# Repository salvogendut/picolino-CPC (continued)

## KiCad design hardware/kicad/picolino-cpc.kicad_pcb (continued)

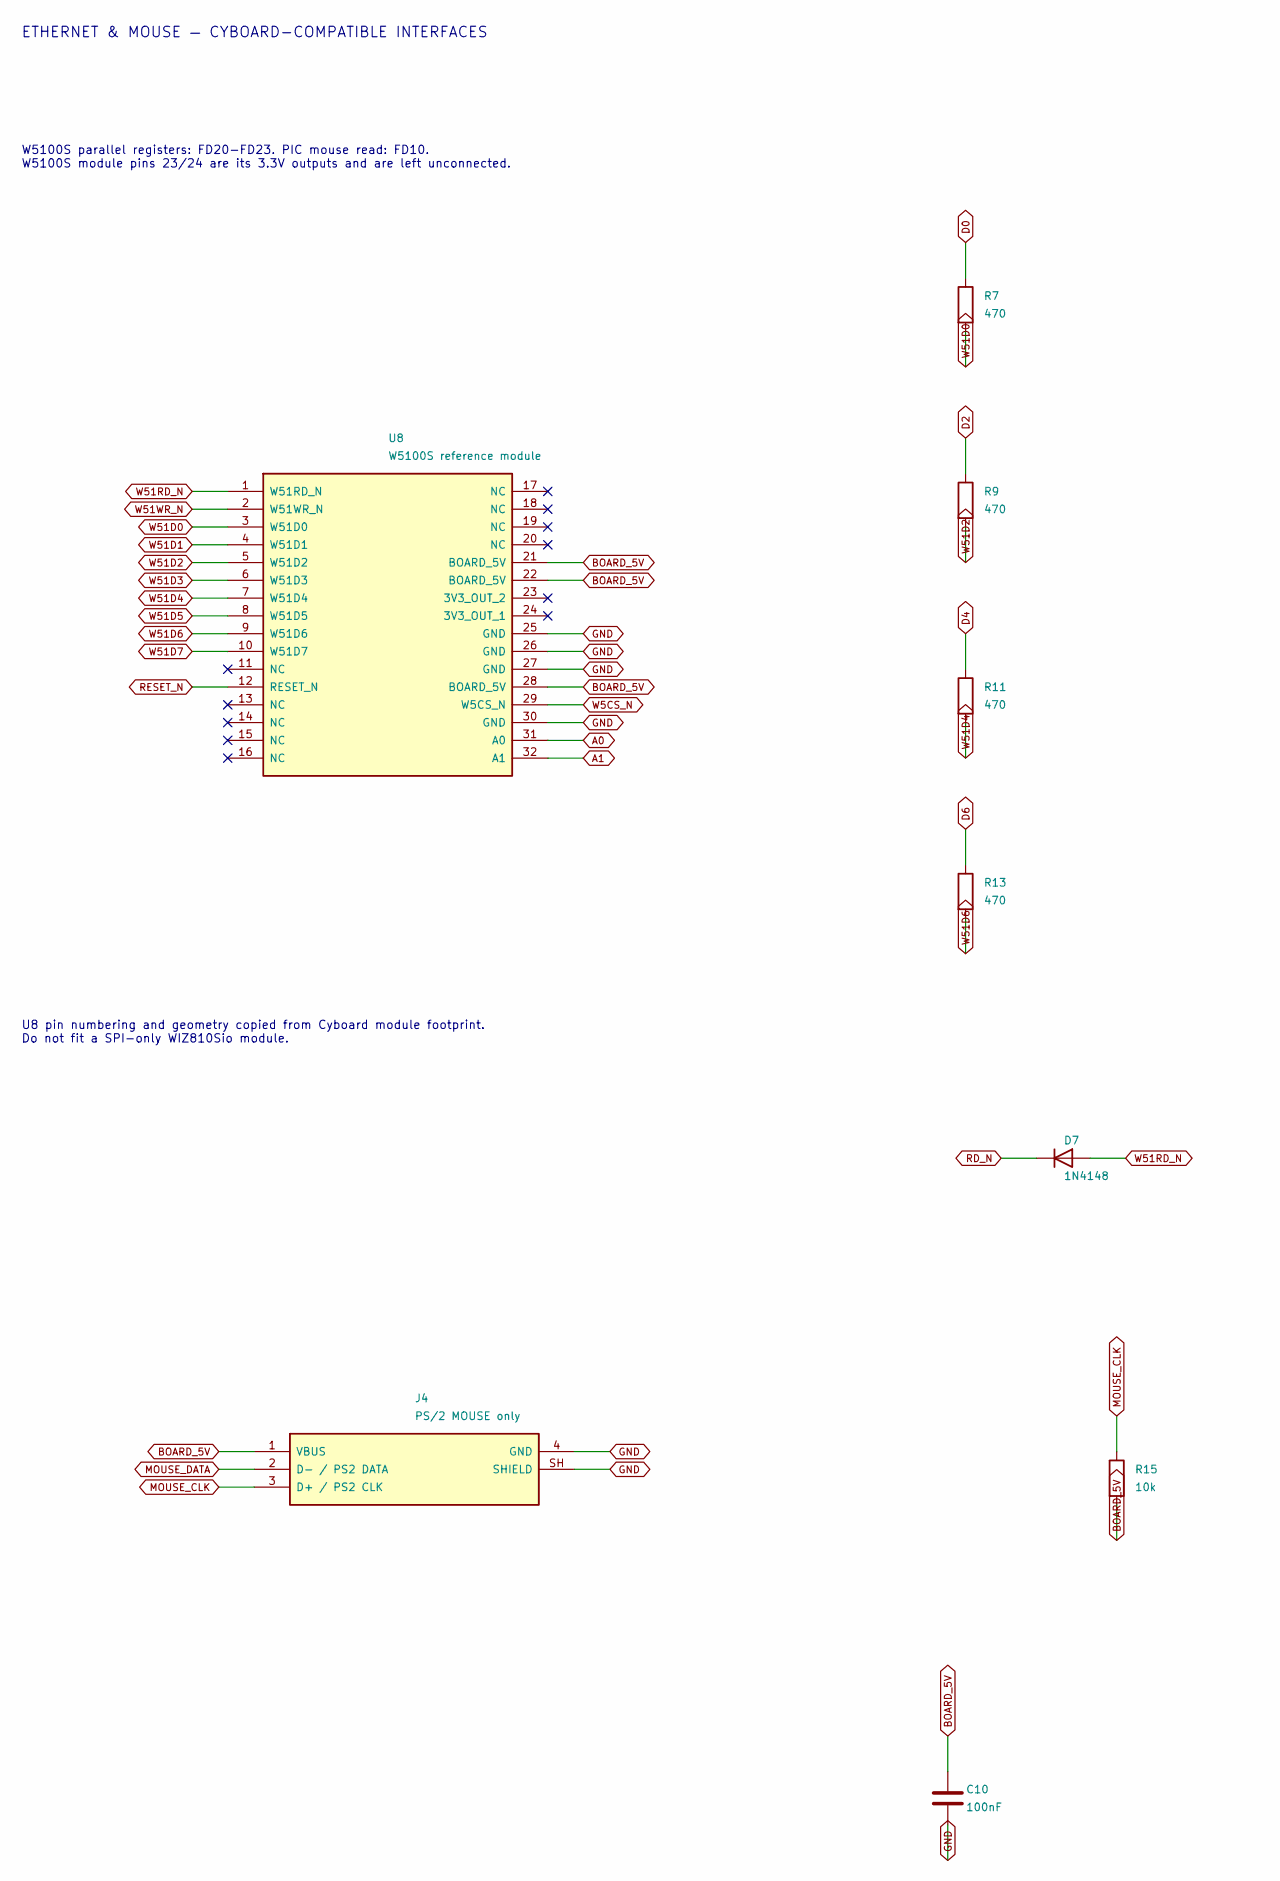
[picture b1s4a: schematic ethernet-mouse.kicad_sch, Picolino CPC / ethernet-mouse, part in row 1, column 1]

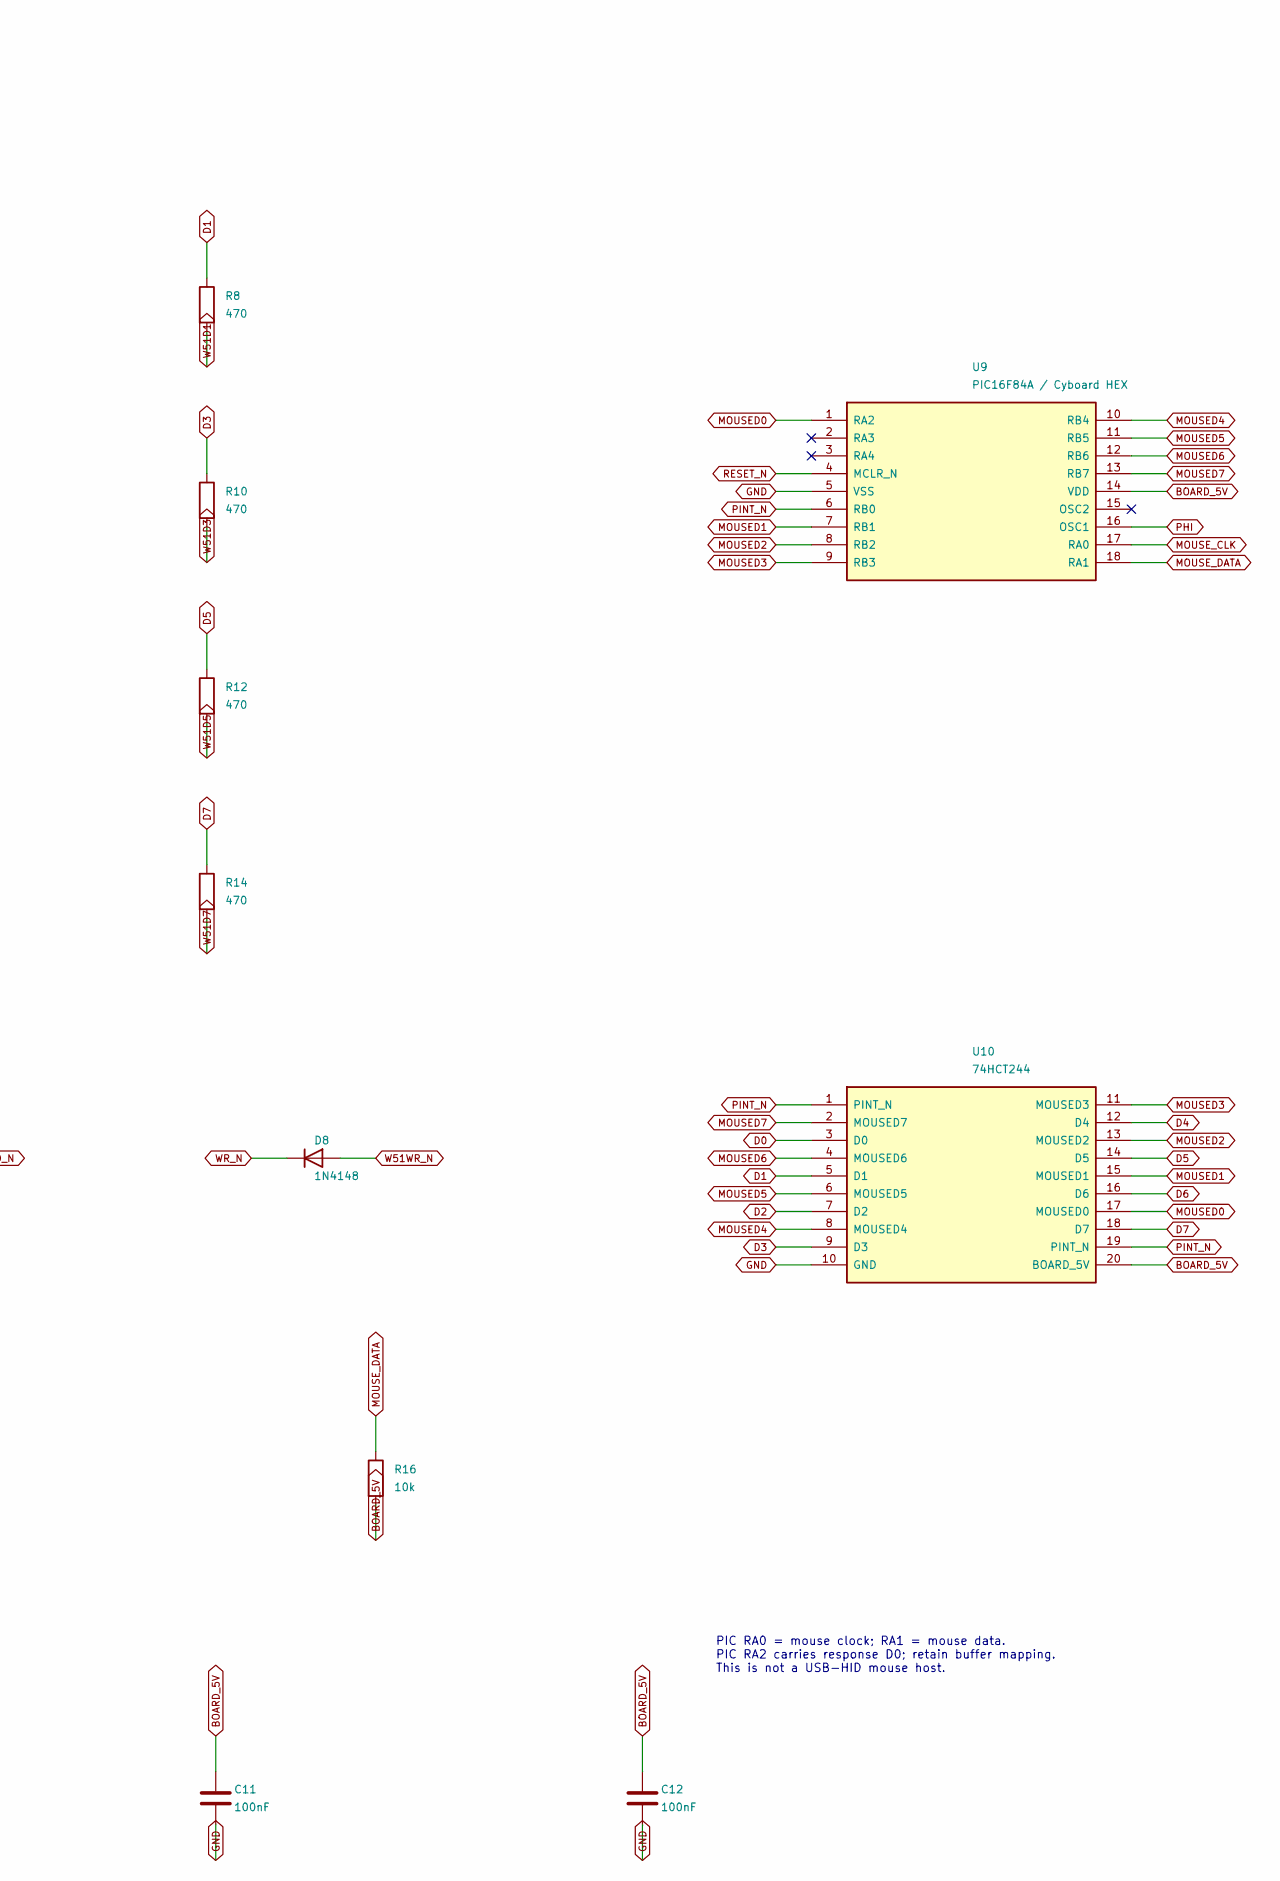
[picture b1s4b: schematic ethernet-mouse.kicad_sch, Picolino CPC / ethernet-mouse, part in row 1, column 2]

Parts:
C10, C11, C12: 100nF; C_0805_2012Metric
D7, D8: 1N4148; D_DO-35_SOD27_P7.62mm_Horizontal
J4: PS/2 MOUSE only; USB_A_TE_292303-7_Horizontal
R7, R8, R9, R10, R11, R12, R13, R14: 470; R_0805_2012Metric
R15, R16: 10k; R_0805_2012Metric
U8: W5100S reference module; W5100S_Cyboard
U9: PIC16F84A / Cyboard HEX; DIP-18_W7.62mm_Socket_LongPads
U10: 74HCT244; DIP-20_W7.62mm_Socket_LongPads

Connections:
A0: U8.31 (A0); also elsewhere on the board
A1: U8.32 (A1); also elsewhere on the board
BOARD_5V: C10.1, C11.1, C12.1, J4.1 (VBUS), R15.2, R16.2, U8.21 (BOARD_5V), U8.22 (BOARD_5V), U8.28 (BOARD_5V), U9.14 (VDD), U10.20 (BOARD_5V); also elsewhere on the board
D0: R7.1, U10.3 (D0); also elsewhere on the board
D1: R8.1, U10.5 (D1); also elsewhere on the board
D2: R9.1, U10.7 (D2); also elsewhere on the board
D3: R10.1, U10.9 (D3); also elsewhere on the board
D4: R11.1, U10.12 (D4); also elsewhere on the board
D5: R12.1, U10.14 (D5); also elsewhere on the board
D6: R13.1, U10.16 (D6); also elsewhere on the board
D7: R14.1, U10.18 (D7); also elsewhere on the board
GND: C10.2, C11.2, C12.2, J4.4 (GND), J4.SH (SHIELD), U8.25 (GND), U8.26 (GND), U8.27 (GND), U8.30 (GND), U9.5 (VSS), U10.10 (GND); also elsewhere on the board
MOUSED0: U9.1 (RA2), U10.17 (MOUSED0)
MOUSED1: U9.7 (RB1), U10.15 (MOUSED1)
MOUSED2: U9.8 (RB2), U10.13 (MOUSED2)
MOUSED3: U9.9 (RB3), U10.11 (MOUSED3)
MOUSED4: U9.10 (RB4), U10.8 (MOUSED4)
MOUSED5: U9.11 (RB5), U10.6 (MOUSED5)
MOUSED6: U9.12 (RB6), U10.4 (MOUSED6)
MOUSED7: U9.13 (RB7), U10.2 (MOUSED7)
MOUSE_CLK: J4.3 (D+ / PS2 CLK), R15.1, U9.17 (RA0)
MOUSE_DATA: J4.2 (D- / PS2 DATA), R16.1, U9.18 (RA1)
PHI: U9.16 (OSC1); also elsewhere on the board
PINT_N: U9.6 (RB0), U10.1 (PINT_N), U10.19 (PINT_N); also elsewhere on the board
RD_N: D7.1 (K); also elsewhere on the board
RESET_N: U8.12 (RESET_N), U9.4 (MCLR_N); also elsewhere on the board
W5CS_N: U8.29 (W5CS_N); also elsewhere on the board
W51D0: R7.2, U8.3 (W51D0)
W51D1: R8.2, U8.4 (W51D1)
W51D2: R9.2, U8.5 (W51D2)
W51D3: R10.2, U8.6 (W51D3)
W51D4: R11.2, U8.7 (W51D4)
W51D5: R12.2, U8.8 (W51D5)
W51D6: R13.2, U8.9 (W51D6)
W51D7: R14.2, U8.10 (W51D7)
W51RD_N: D7.2 (A), U8.1 (W51RD_N)
W51WR_N: D8.2 (A), U8.2 (W51WR_N)
WR_N: D8.1 (K); also elsewhere on the board

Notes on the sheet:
ETHERNET & MOUSE — CYBOARD-COMPATIBLE INTERFACES
W5100S parallel registers: FD20-FD23. PIC mouse read: FD10. W5100S module pins 23/24 are its 3.3V outputs and are left unconnected.
U8 pin numbering and geometry copied from Cyboard module footprint. Do not fit a SPI-only WIZ810Sio module.
PIC RA0 = mouse clock; RA1 = mouse data. PIC RA2 carries response D0; retain buffer mapping. This is not a USB-HID mouse host.

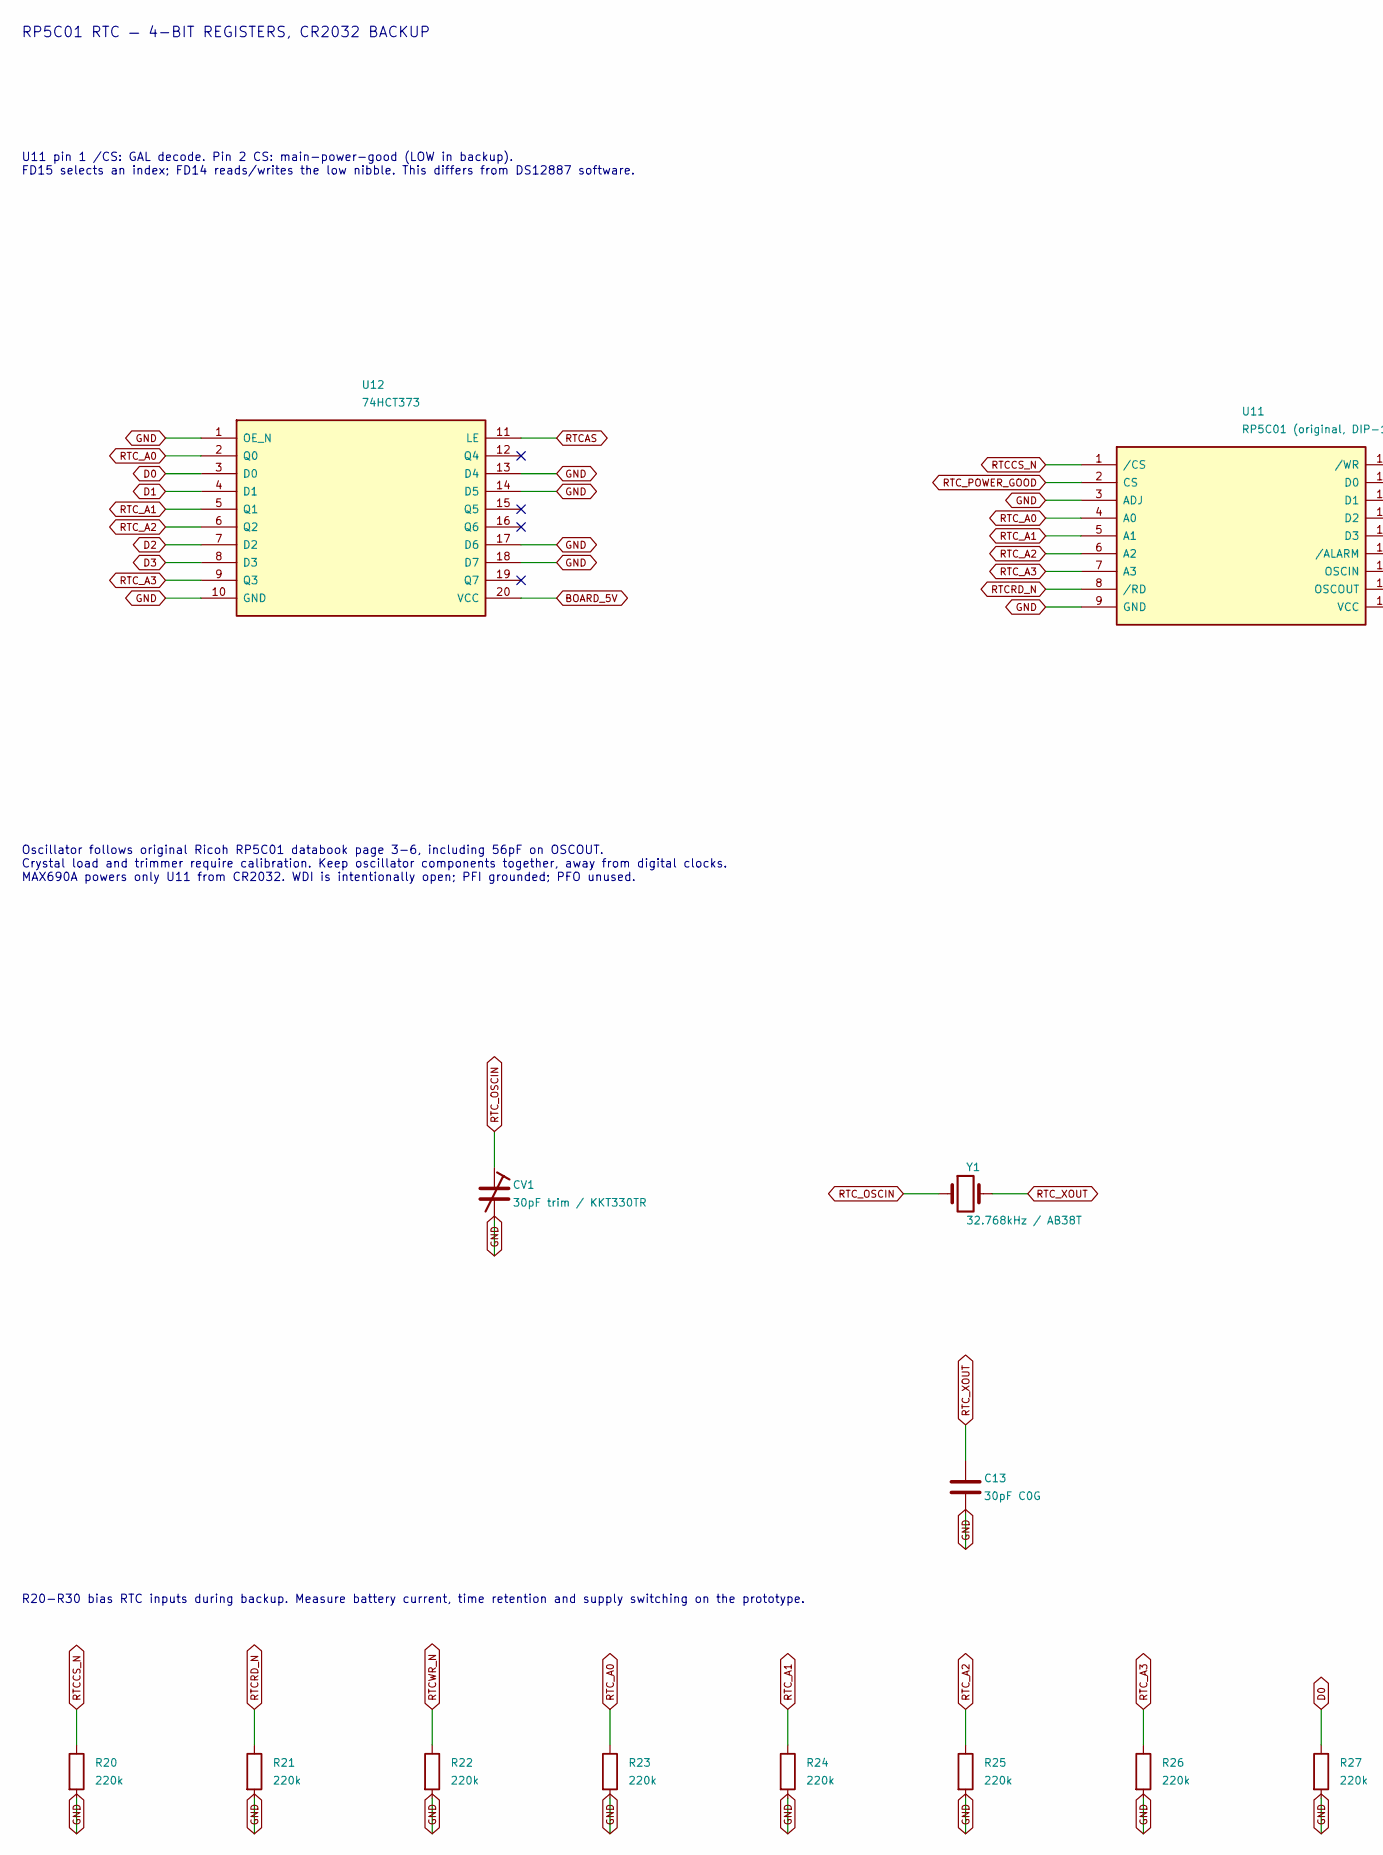
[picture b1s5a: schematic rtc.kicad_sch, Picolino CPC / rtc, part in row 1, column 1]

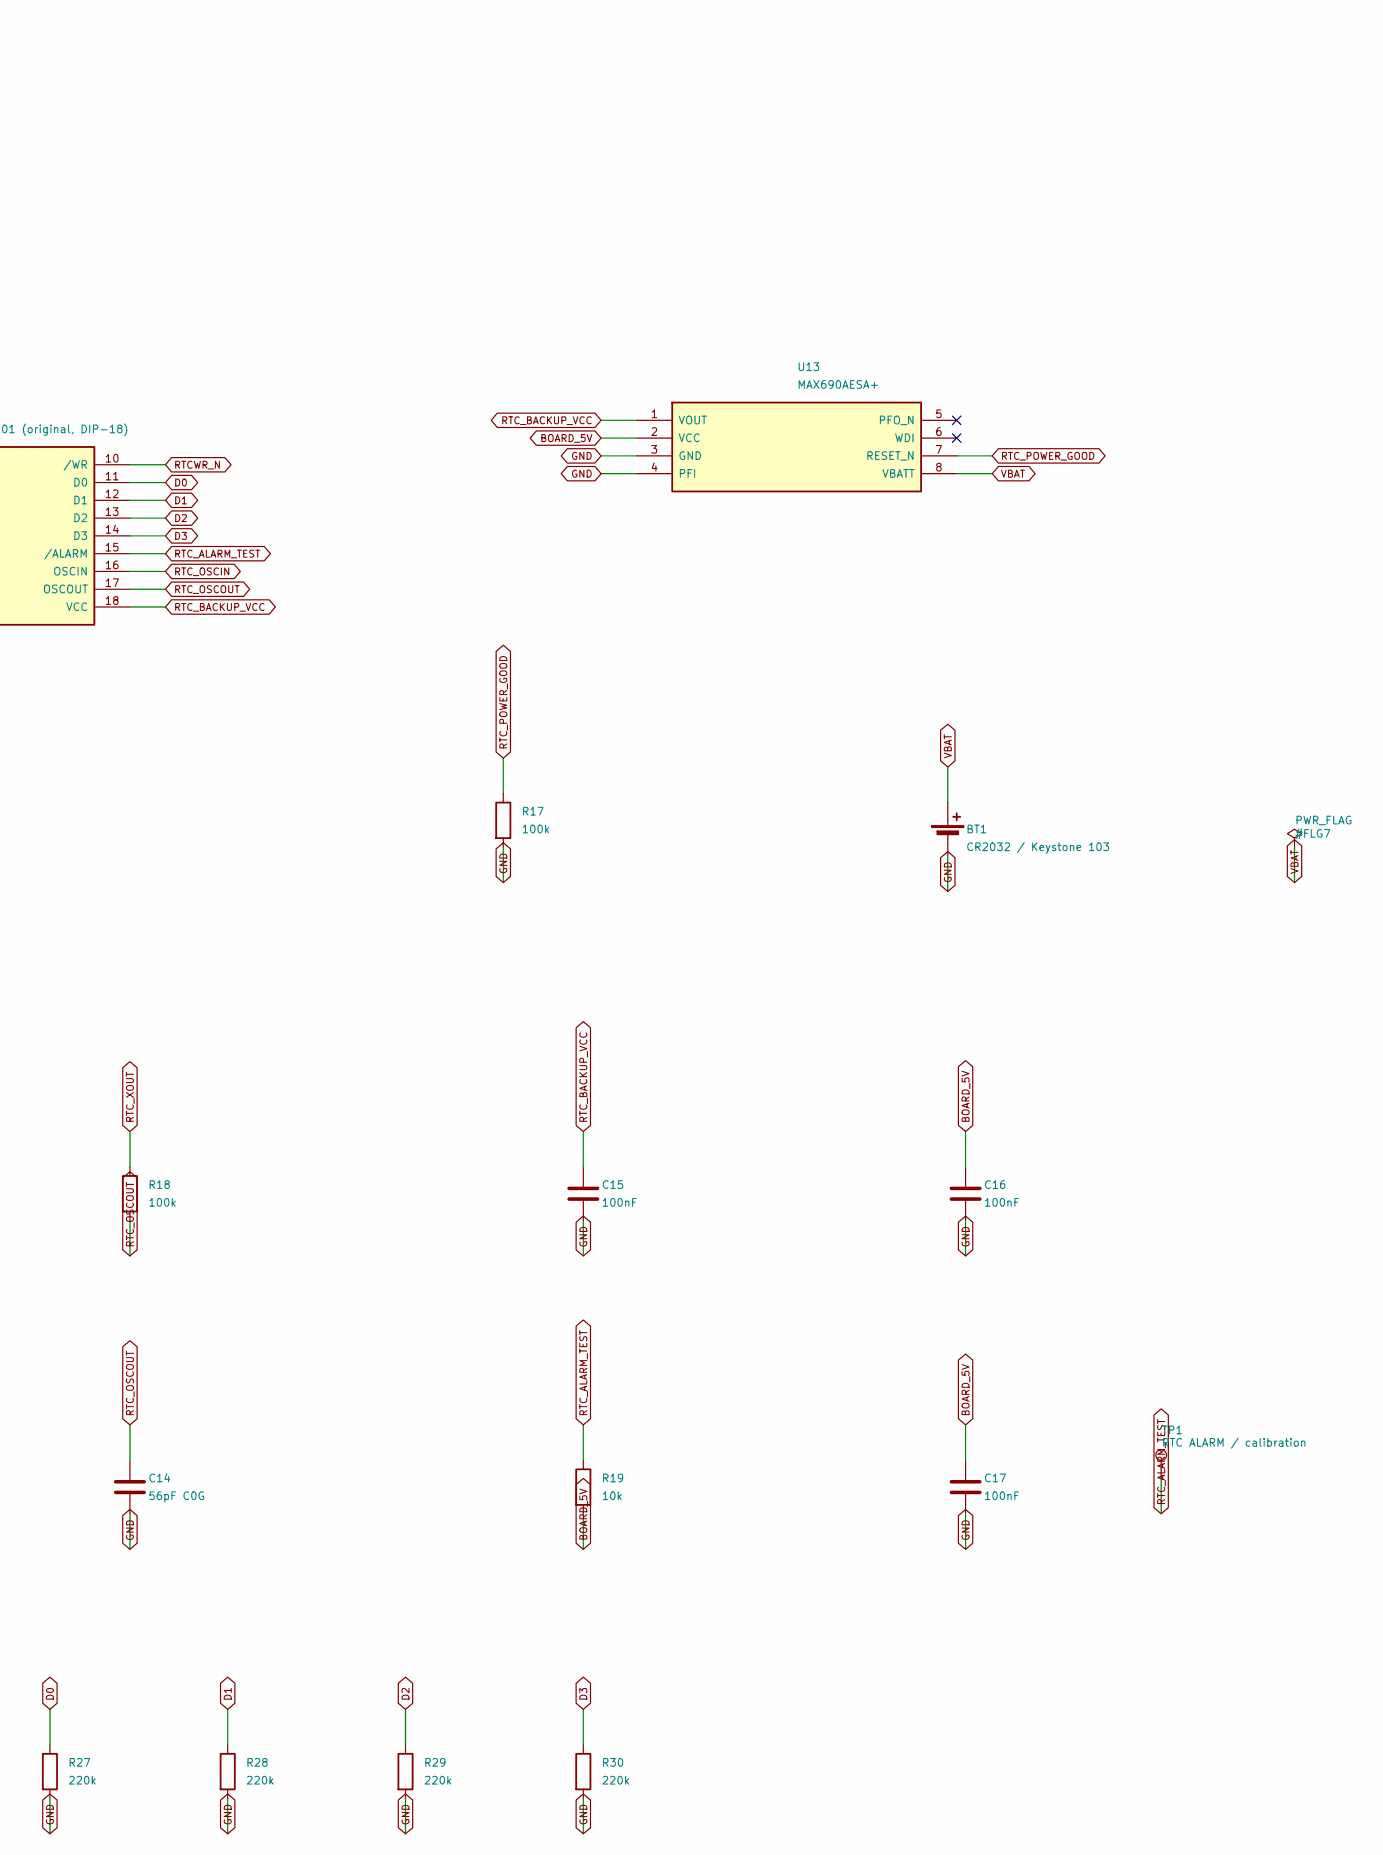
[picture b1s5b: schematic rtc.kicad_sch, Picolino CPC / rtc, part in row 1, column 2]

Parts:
BT1: CR2032 / Keystone 103; BatteryHolder_Keystone_103_1x20mm
C13: 30pF C0G; C_0805_2012Metric
C14: 56pF C0G; C_0805_2012Metric
C15, C16, C17: 100nF; C_0805_2012Metric
CV1: 30pF trim / KKT330TR; C_Trimmer_Murata_TZC3
R17, R18: 100k; R_0805_2012Metric
R19: 10k; R_0805_2012Metric
R20, R21, R22, R23, R24, R25, R26, R27, R28, R29, R30: 220k; R_0805_2012Metric
TP1: RTC ALARM / calibration; TestPoint_THTPad_D2.0mm_Drill1.0mm
U11: RP5C01 (original, DIP-18); DIP-18_W7.62mm_Socket_LongPads
U12: 74HCT373; DIP-20_W7.62mm_Socket_LongPads
U13: MAX690AESA+; SOIC-8_3.9x4.9mm_P1.27mm
Y1: 32.768kHz / AB38T; Crystal_C38-LF_D3.0mm_L8.0mm_Vertical

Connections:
BOARD_5V: C16.1, C17.1, R19.2, U12.20 (VCC), U13.2 (VCC); also elsewhere on the board
D0: R27.1, U11.11 (D0), U12.3 (D0); also elsewhere on the board
D1: R28.1, U11.12 (D1), U12.4 (D1); also elsewhere on the board
D2: R29.1, U11.13 (D2), U12.7 (D2); also elsewhere on the board
D3: R30.1, U11.14 (D3), U12.8 (D3); also elsewhere on the board
GND: BT1.2 (-), C13.2, C14.2, C15.2, C16.2, C17.2, CV1.2, R17.2, R20.2, R21.2, R22.2, R23.2, R24.2, R25.2, R26.2, R27.2, R28.2, R29.2, R30.2, U11.3 (ADJ), U11.9 (GND), U12.1 (OE_N), U12.10 (GND), U12.13 (D4), U12.14 (D5), U12.17 (D6), U12.18 (D7), U13.3 (GND), U13.4 (PFI); also elsewhere on the board
RTCAS: U12.11 (LE); also elsewhere on the board
RTCCS_N: R20.1, U11.1 (/CS); also elsewhere on the board
RTCRD_N: R21.1, U11.8 (/RD); also elsewhere on the board
RTCWR_N: R22.1, U11.10 (/WR); also elsewhere on the board
RTC_A0: R23.1, U11.4 (A0), U12.2 (Q0)
RTC_A1: R24.1, U11.5 (A1), U12.5 (Q1)
RTC_A2: R25.1, U11.6 (A2), U12.6 (Q2)
RTC_A3: R26.1, U11.7 (A3), U12.9 (Q3)
RTC_ALARM_TEST: R19.1, TP1.1, U11.15 (/ALARM)
RTC_BACKUP_VCC: C15.1, U11.18 (VCC), U13.1 (VOUT)
RTC_OSCIN: CV1.1, U11.16 (OSCIN), Y1.1
RTC_OSCOUT: C14.1, R18.2, U11.17 (OSCOUT)
RTC_POWER_GOOD: R17.1, U11.2 (CS), U13.7 (RESET_N)
RTC_XOUT: C13.1, R18.1, Y1.2
VBAT: BT1.1 (+), U13.8 (VBATT)

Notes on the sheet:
RP5C01 RTC — 4-BIT REGISTERS, CR2032 BACKUP
U11 pin 1 /CS: GAL decode. Pin 2 CS: main-power-good (LOW in backup). FD15 selects an index; FD14 reads/writes the low nibble. This differs from DS12887 software.
Oscillator follows original Ricoh RP5C01 databook page 3-6, including 56pF on OSCOUT. Crystal load and trimmer require calibration. Keep oscillator components together, away from digital clocks. MAX690A powers only U11 from CR2032. WDI is intentionally open; PFI grounded; PFO unused.
R20-R30 bias RTC inputs during backup. Measure battery current, time retention and supply switching on the prototype.

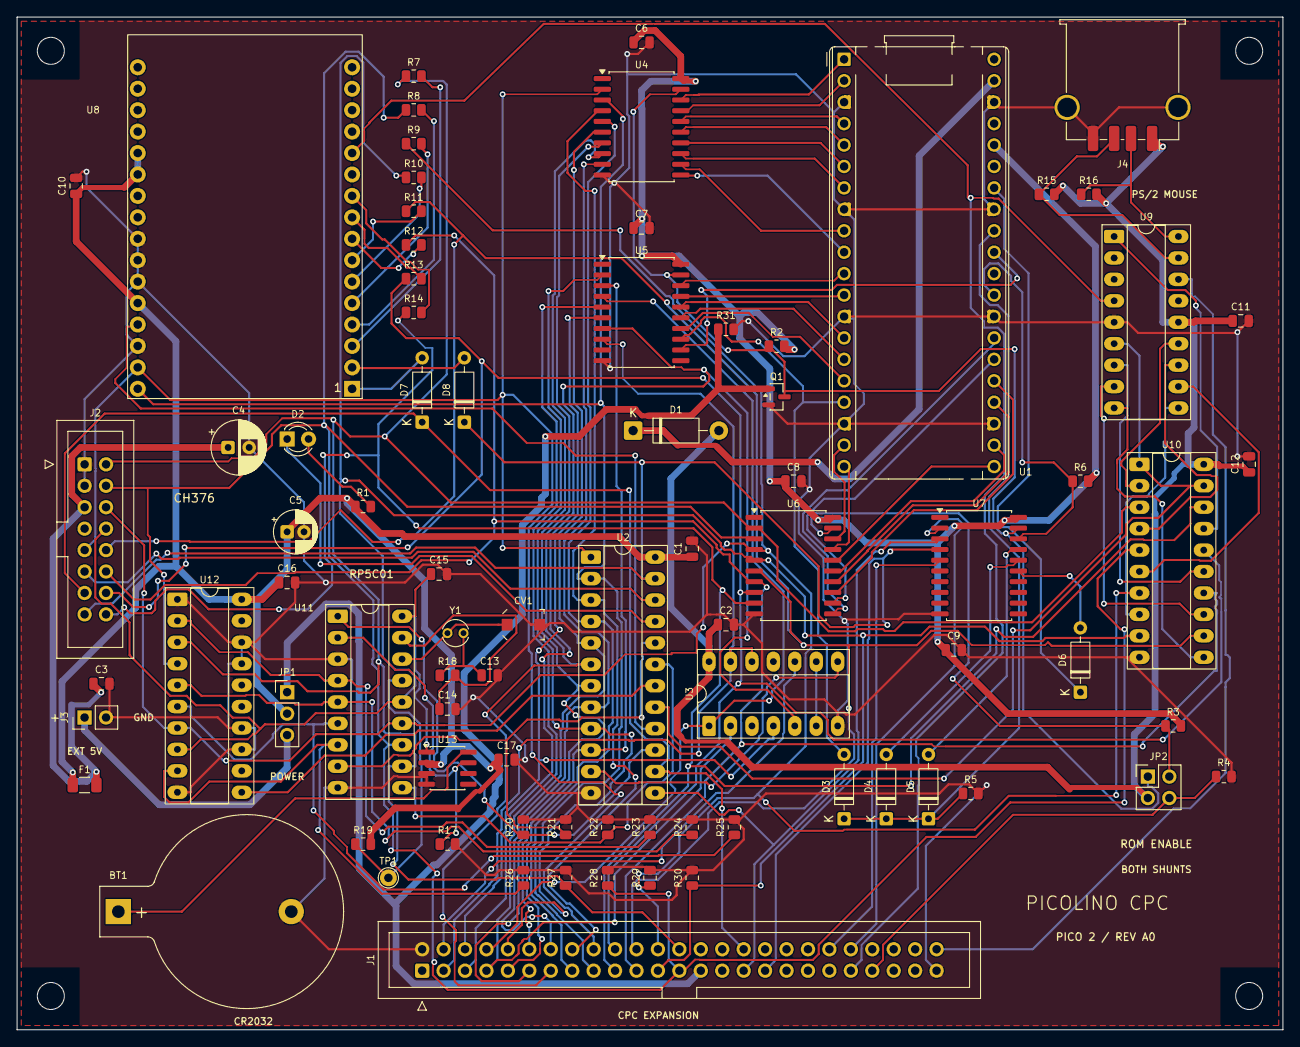
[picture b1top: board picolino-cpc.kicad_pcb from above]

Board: 2 copper layers, 150.0 x 120.0 mm, 85 parts (0 on the bottom side), 112 nets.

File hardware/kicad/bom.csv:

Reference,Value,Footprint,Assembly note
J1,CPC 50-pin expansion,Picolino:IDC-Header_2x25_P2.54mm_Vertical,CPC/Mother X4 contact numbers; short 50-way cable. Pin 1 marked on silk.
U2,GAL20V8B / picolino.jed,Picolino:DIP-24_W7.62mm_Socket_LongPads,Program firmware/gal/picolino.pld before fitting.
U3,74HCT21,Picolino:DIP-14_W7.62mm_Socket_LongPads,
J2,CH376 parallel / short ribbon,Picolino:IDC-Header_2x08_P2.54mm_Vertical,CPC_PICOROM J2 pinout. External reference CH376 module; pin 7 unused.
J3,EXT regulated 5V,Picolino:PinHeader_1x02_P2.54mm_Vertical,
JP1,POWER: 1 CPC / 2 BOARD / 3 EXT,Picolino:PinHeader_1x03_P2.54mm_Vertical,Fit ONE shunt only; use 2-3 for external board power.
F1,USB 500mA hold,Picolino:Fuse_1206_3216Metric,Example Bourns MF-NSMF050-2; validate inrush and voltage drop with chosen USB drive.
D1,1N5817,Picolino:D_DO-41_SOD81_P10.16mm_Horizontal,Cathode/band at Pico VSYS; prevents Pico USB feeding board 5V.
R1,1k,Picolino:R_0805_2012Metric,
D2,USB activity,Picolino:LED_D3.0mm,
C1,100nF,Picolino:C_0805_2012Metric,
C2,100nF,Picolino:C_0805_2012Metric,
C3,100nF,Picolino:C_0805_2012Metric,
C4,100uF / 10V,Picolino:CP_Radial_D6.3mm_P2.50mm,
C5,47uF / 10V,Picolino:CP_Radial_D5.0mm_P2.00mm,
U1,Raspberry Pi Pico 2,Picolino:Pico2_Socketed,"Two 1x20 sockets, 17.78mm row spacing; USB faces top edge."
U4,SN74CB3T3245DW,Picolino:SOIC-20W_7.5x12.8mm_P1.27mm,Exact CB3T level-translating part at 3.3V; not HC245 or CB3Q.
C6,100nF,Picolino:C_0805_2012Metric,
U5,SN74CB3T3245DW,Picolino:SOIC-20W_7.5x12.8mm_P1.27mm,Exact CB3T level-translating part at 3.3V; not HC245 or CB3Q.
C7,100nF,Picolino:C_0805_2012Metric,
U6,SN74CB3T3245DW,Picolino:SOIC-20W_7.5x12.8mm_P1.27mm,Exact CB3T level-translating part at 3.3V; not HC245 or CB3Q.
C8,100nF,Picolino:C_0805_2012Metric,
U7,SN74CB3T3245DW,Picolino:SOIC-20W_7.5x12.8mm_P1.27mm,Exact CB3T level-translating part at 3.3V; not HC245 or CB3Q.
C9,100nF,Picolino:C_0805_2012Metric,
JP2,ROM ENABLE: fit BOTH shunts,Picolino:PinHeader_2x02_P2.54mm_Vertical,Both open: internal CPC ROMs and input-only monitor. Both fitted: RP2350 ROM firmware required.
Q1,2N7002,Picolino:SOT-23,CPC power gates all bus switches; Pico USB alone cannot enable them.
R31,100k,Picolino:R_0805_2012Metric,Gate discharge when the CPC expansion cable is disconnected.
R2,10k,Picolino:R_0805_2012Metric,
R3,10k,Picolino:R_0805_2012Metric,
R4,10k,Picolino:R_0805_2012Metric,
D3,BAT43,Picolino:D_DO-35_SOD27_P7.62mm_Horizontal,Band at ROM_LATCH; active-low capture when all three inputs are low.
D4,BAT43,Picolino:D_DO-35_SOD27_P7.62mm_Horizontal,Band at ROM_LATCH; active-low capture when all three inputs are low.
D5,BAT43,Picolino:D_DO-35_SOD27_P7.62mm_Horizontal,Band at ROM_LATCH; active-low capture when all three inputs are low.
R5,2.2k,Picolino:R_0805_2012Metric,
D6,BAT43,Picolino:D_DO-35_SOD27_P7.62mm_Horizontal,Band at GPIO28; firmware may only pull reset low or release it.
R6,10k,Picolino:R_0805_2012Metric,
U8,W5100S reference module,Picolino:W5100S_Cyboard,"Two 1x16 sockets, 25.4mm row spacing. Reference module has a 3.3V regulator. RJ45 faces top edge."
R7,470,Picolino:R_0805_2012Metric,
R8,470,Picolino:R_0805_2012Metric,
R9,470,Picolino:R_0805_2012Metric,
R10,470,Picolino:R_0805_2012Metric,
R11,470,Picolino:R_0805_2012Metric,
R12,470,Picolino:R_0805_2012Metric,
R13,470,Picolino:R_0805_2012Metric,
R14,470,Picolino:R_0805_2012Metric,
D7,1N4148,Picolino:D_DO-35_SOD27_P7.62mm_Horizontal,Cyboard read/write conditioning; cathode at CPC strobe.
D8,1N4148,Picolino:D_DO-35_SOD27_P7.62mm_Horizontal,Cyboard read/write conditioning; cathode at CPC strobe.
U9,PIC16F84A / Cyboard HEX,Picolino:DIP-18_W7.62mm_Socket_LongPads,"Retain original PIC firmware, config fuses and CPC PHI clock."
U10,74HCT244,Picolino:DIP-20_W7.62mm_Socket_LongPads,
J4,PS/2 MOUSE only,Picolino:USB_A_TE_292303-7_Horizontal,USB-shaped socket carries PS/2 protocol; only a PS/2-capable mouse works.
R15,10k,Picolino:R_0805_2012Metric,
R16,10k,Picolino:R_0805_2012Metric,
C10,100nF,Picolino:C_0805_2012Metric,
C11,100nF,Picolino:C_0805_2012Metric,
C12,100nF,Picolino:C_0805_2012Metric,
U11,"RP5C01 (original, DIP-18)",Picolino:DIP-18_W7.62mm_Socket_LongPads,
U12,74HCT373,Picolino:DIP-20_W7.62mm_Socket_LongPads,LE high only on FD15 write; closes at end of write. Unused data inputs grounded.
U13,MAX690AESA+,Picolino:SOIC-8_3.9x4.9mm_P1.27mm,"Pin 7 /RESET is HIGH when main power is valid, directly enabling RTC CS. WDI left open to disable watchdog."
BT1,CR2032 / Keystone 103,Picolino:BatteryHolder_Keystone_103_1x20mm,"Single CR2032, positive face up. No charging circuit."
R17,100k,Picolino:R_0805_2012Metric,Defines disabled state below supervisor operating voltage.
Y1,32.768kHz / AB38T,Picolino:Crystal_C38-LF_D3.0mm_L8.0mm_Vertical,"AB38T-32.768KHZ, 12.5pF load; gently form leads from 0.8mm to 1.9mm pitch. Local pads enlarged to 0.7mm drill. Calibrate on PCB."
R18,100k,Picolino:R_0805_2012Metric,
CV1,30pF trim / KKT330TR,Picolino:C_Trimmer_Murata_TZC3,"Kingtronics KKT330TR: minimum setting <=8pF, maximum >=28.5pF; TZC3-compatible geometry. Calibrate from ALARM output; verify trim range."
C13,30pF C0G,Picolino:C_0805_2012Metric,
C14,56pF C0G,Picolino:C_0805_2012Metric,
C15,100nF,Picolino:C_0805_2012Metric,
C16,100nF,Picolino:C_0805_2012Metric,
C17,100nF,Picolino:C_0805_2012Metric,
R19,10k,Picolino:R_0805_2012Metric,
TP1,RTC ALARM / calibration,Picolino:TestPoint_THTPad_D2.0mm_Drill1.0mm,
R20,220k,Picolino:R_0805_2012Metric,RTC backup input bias; no pull-up to battery supply.
R21,220k,Picolino:R_0805_2012Metric,RTC backup input bias; no pull-up to battery supply.
R22,220k,Picolino:R_0805_2012Metric,RTC backup input bias; no pull-up to battery supply.
R23,220k,Picolino:R_0805_2012Metric,RTC backup input bias; no pull-up to battery supply.
R24,220k,Picolino:R_0805_2012Metric,RTC backup input bias; no pull-up to battery supply.
R25,220k,Picolino:R_0805_2012Metric,RTC backup input bias; no pull-up to battery supply.
R26,220k,Picolino:R_0805_2012Metric,RTC backup input bias; no pull-up to battery supply.
R27,220k,Picolino:R_0805_2012Metric,RTC backup input bias; no pull-up to battery supply.
R28,220k,Picolino:R_0805_2012Metric,RTC backup input bias; no pull-up to battery supply.
R29,220k,Picolino:R_0805_2012Metric,RTC backup input bias; no pull-up to battery supply.
R30,220k,Picolino:R_0805_2012Metric,RTC backup input bias; no pull-up to battery supply.
H1,M3 NPTH,Picolino:MountingHole_3.2mm_M3,
H2,M3 NPTH,Picolino:MountingHole_3.2mm_M3,
H3,M3 NPTH,Picolino:MountingHole_3.2mm_M3,
H4,M3 NPTH,Picolino:MountingHole_3.2mm_M3,

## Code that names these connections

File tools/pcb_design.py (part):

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    part('C'+str(i),'C',value,CAP,{1:a,2:b},sheet,sch,pcb,note)

# Sheet 1: verified expansion contact numbering, full address decode, supply selection.
cpc={p:net(n) for p,n in IFACE['cpc']['pins'].items()};cpc['27']='CPC_5V'
part('J1','CPC_BUS','CPC 50-pin expansion','Connector_IDC:IDC-Header_2x25_P2.54mm_Vertical',cpc,1,(65,108),(143,209,90),
     'CPC/Mother X4 contact numbers; short 50-way cable. Pin 1 marked on silk.')
gal={i+1:f'A{i}' for i in range(10)}
gal.update({11:'A1X',12:'GND',13:'IORQ_N',14:'RD_N',15:'RTCCS_N',16:'W5CS_N',17:'PINT_N',
    18:'RTCAS',19:'RTCWR_N',20:'RTCRD_N',21:'CHLED_N',22:'CHCS_N',23:'WR_N',24:'BOARD_5V'})
part('U2','GAL20V8','GAL20V8B / picolino.jed',DIP(24),gal,1,(185,91),(157,164,0),'Program firmware/gal/picolino.pld before fitting.')
hct={1:'A10',2:'A11',4:'A12',5:'A13',6:'A10_13',7:'GND',8:'A1X',9:'A10_13',10:'A14',12:'A15',13:'A15',14:'BOARD_5V'}
part('U3','HCT21','74HCT21',DIP(14),hct,1,(295,84),(182,184,90))
ch={p:net(n) for p,n in IFACE['ch376']['pins'].items() if n!='NC'};ch['5']='USB_5V'
part('J2','CH376_HEADER','CH376 parallel / short ribbon','Connector_IDC:IDC-Header_2x08_P2.54mm_Vertical',ch,1,(295,157),(113,132,0),
     'CPC_PICOROM J2 pinout. External reference CH376 module; pin 7 unused.')
part('J3','Conn_01x02','EXT regulated 5V',HDR+'PinHeader_1x02_P2.54mm_Vertical',{1:'EXT_5V',2:'GND'},1,(62,220),(114,160,90))
part('JP1','Conn_01x03','POWER: 1 CPC / 2 BOARD / 3 EXT',HDR+'PinHeader_1x03_P2.54mm_Vertical',
     {1:'CPC_5V',2:'BOARD_5V',3:'EXT_5V'},1,(164,209),(125,165,0),'Fit ONE shunt only; use 2-3 for external board power.')
part('F1','Polyfuse','USB 500mA hold','Fuse:Fuse_1206_3216Metric',{1:'BOARD_5V',2:'USB_5V'},1,(245,215),(114,148,0),
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 (20,187,'JP1 selects the board supply; never bridge all three pins.\nExternal input: regulated 5V only; common CPC ground. Power CPC before external board supply.\nCheck power budget before selecting CPC power; external 5V is preferred for USB-drive bring-up.')]

# Sheet 2: all 26 exposed GPIOs, input monitoring independent of ROM enable.
pico={str(p['module_pin']):('P_'+net(p['signal']) if p['signal'] not in ('ROM_LATCH','RESET_PULLDOWN') else p['signal']) for p in IFACE['pico2']['gpio']}
pico.update({str(p):'GND' for p in IFACE['pico2']['ground_pins']});pico.update({'36':'PICO_3V3','39':'PICO_VSYS'})
part('U1','Pico2','Raspberry Pi Pico 2','Local:Pico2_Socketed',pico,2,(327,102),(198,105,0),'Two 1x20 sockets, 17.78mm row spacing; USB faces top edge.')
groups=[[f'A{i}' for i in range(8)],[f'A{i}' for i in range(8,14)]+['A15'],[f'D{i}' for i in range(8)],['ROMEN_N','IORQ_N','WR_N','BUSRESET_N']]
for i,signals in enumerate(groups):
    pins={10:'GND',19:'DATA_OE_N' if i==2 else 'INPUT_OE_N',20:'PICO_3V3'}
    for channel,n in enumerate(signals,1):pins[channel+1]=n;pins[19-channel]='P_'+n
    part('U'+str(4+i),'CB3T3245','SN74CB3T3245DW','Package_SO:SOIC-20W_7.5x12.8mm_P1.27mm',pins,2,
        (73+i%2*116,75+i//2*77),[(174,113,0),(174,135,0),(192,165,0),(214,165,0)][i],
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for i,a,sch,pcb in [(3,'P_A13',(70,280),(197,181,90)),(4,'P_WR_N',(145,280),(202,181,90)),(5,'P_IORQ_N',(220,280),(207,181,90))]:
    part('D'+str(i),'D_Schottky','BAT43','Diode_THT:D_DO-35_SOD27_P7.62mm_Horizontal',{1:'ROM_LATCH',2:a},2,sch,pcb,'Band at ROM_LATCH; active-low capture when all three inputs are low.')
resistor(5,'2.2k','ROM_LATCH','GND',2,(299,250),(211,180,0))
part('D6','D_Schottky','BAT43','Diode_THT:D_DO-35_SOD27_P7.62mm_Horizontal',{1:'RESET_PULLDOWN',2:'P_BUSRESET_N'},2,(356,250),(230,178,90),'Band at GPIO28; firmware may only pull reset low or release it.')
resistor(6,'10k','P_ROMEN_N','PICO_3V3',2,(360,211),(227,149,0))
NOTES[2]=[(20,15,'PICO 2 / RP2350 — ROM INTERFACE'),(20,32,'3.3V B-side signals have P_ prefix. All CPC-facing GPIOs use level translation.\nInput switches enable when CPC 5V is present; JP2 separately isolates the data bus and controls ROMDIS.'),
 (284,145,'Native RP2350 monitor: keep JP2 open.\nROM-serving firmware and timing remain to be validated.'),
 (20,234,'U4-U7 each require local 100nF. GPIO0/1 are address inputs: UART stdio must stay disabled.')]

# Sheet 3: original Cyboard parallel Ethernet conditioning and PIC-to-buffer map.
w={p:net(n) for p,n in IFACE['w5100s']['pins'].items() if p not in ['23','24']};w['29']='W5CS_N'
part('U8','W5100S_Module','W5100S reference module','Local:W5100S_Cyboard',w,3,(73,100),(127,125,180),
     'Two 1x16 sockets, 25.4mm row spacing. Reference module has a 3.3V regulator. RJ45 faces top edge.')
for i in range(8):resistor(7+i,'470',f'D{i}',f'W51D{i}',3,(155+(i%2)*58,54+(i//2)*28),(147,107+i*4,0))
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NOTES[3]=[(20,15,'ETHERNET & MOUSE — CYBOARD-COMPATIBLE INTERFACES'),
 (20,32,'W5100S parallel registers: FD20-FD23. PIC mouse read: FD10.\nW5100S module pins 23/24 are its 3.3V outputs and are left unconnected.'),
 (20,157,'U8 pin numbering and geometry copied from Cyboard module footprint.\nDo not fit a SPI-only WIZ810Sio module.'),
 (286,245,'PIC RA0 = mouse clock; RA1 = mouse data.\nPIC RA2 carries response D0; retain buffer mapping.\nThis is not a USB-HID mouse host.')]

# Sheet 4: original (non-A) RP5C01 circuit, stable index latch and backup inhibit.
rtc={p:net(n) for p,n in IFACE['rp5c01']['proposed_connections'].items()}
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      'Pico2':device_pins(40,pico_names,bidir=[int(p['module_pin']) for p in IFACE['pico2']['gpio']],inputs=[30,37],power_in=[39,40],power_out=[36]),
      'CB3T3245':device_pins(20,{1:'NC',10:'GND',19:'OE_N',20:'VCC',**{i+1:f'A{i}' for i in range(1,9)},**{19-i:f'B{i}' for i in range(1,9)}},inputs=[19],bidir=[*range(2,10),*range(11,19)],power_in=[10,20],nc=[1]),
      'W5100S_Module':device_pins(32,{**w,'23':'3V3_OUT_2','24':'3V3_OUT_1'},inputs=[1,2,12,28,29,30,31,32],bidir=range(3,11),power_in=[21,22,25,26,27],power_out=[23,24]),
      'PIC16F84A':device_pins(18,{**{str(i):f'RA{i-17}' for i in [17,18]},1:'RA2',2:'RA3',3:'RA4',4:'MCLR_N',5:'VSS',**{i:f'RB{i-6}' for i in range(6,14)},14:'VDD',15:'OSC2',16:'OSC1'},inputs=[4,16],outputs=[15],bidir=[1,2,3,17,18,*range(6,14)],power_in=[5,14]),
      'HCT244':device_pins(20,buf,inputs=[1,2,4,6,8,11,13,15,17,19],tri=[3,5,7,9,12,14,16,18],power_in=[10,20]),
      'USB_Mouse':[(1,'VBUS','passive'),(2,'D- / PS2 DATA','passive'),(3,'D+ / PS2 CLK','passive'),(4,'GND','passive'),('SH','SHIELD','passive')],
      'HCT373':device_pins(20,{1:'OE_N',2:'Q0',3:'D0',4:'D1',5:'Q1',6:'Q2',7:'D2',8:'D3',9:'Q3',10:'GND',11:'LE',12:'Q4',13:'D4',14:'D5',15:'Q5',16:'Q6',17:'D6',18:'D7',19:'Q7',20:'VCC'},inputs=[1,3,4,7,8,11,13,14,17,18],tri=[2,5,6,9,12,15,16,19],power_in=[10,20]),
      'RP5C01':device_pins(18,IFACE['rp5c01']['pins'],inputs=[1,2,3,4,5,6,7,8,10,16],outputs=[15,17],bidir=range(11,15),power_in=[9,18]),
      'MAX690A':device_pins(8,{1:'VOUT',2:'VCC',3:'GND',4:'PFI',5:'PFO_N',6:'WDI',7:'RESET_N',8:'VBATT'},inputs=[4,6],outputs=[5,7],power_in=[2,3,8],power_out=[1]),
      '2N7002':device_pins(3,{1:'G',2:'S',3:'D'},inputs=[1])}
    symbols += [custom_symbol(n,p) for n,p in definitions.items()]
    (folder/f'{LIB}.kicad_sym').write_text('(kicad_symbol_lib (version 20241209) (generator "kicad_symbol_editor")\n'+'\n'.join(dumps(s) for s in symbols)+'\n)\n')
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
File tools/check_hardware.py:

#!/usr/bin/env python3
"""Independent netlist/pad checks against firmware and imported source pin maps."""
import json
from pathlib import Path
import sys
import xml.etree.ElementTree as ET
from pcb_sexpr import loads, child, children
from galasm_source import parse

ROOT=Path(__file__).resolve().parents[1]
CAD=ROOT/'hardware/kicad'
interface=json.loads((ROOT/'hardware/interfaces.json').read_text())
nets={}
for n in ET.parse(CAD/'checks/netlist.xml').findall('./nets/net'):
    for node in n.findall('node'):nets[(node.get('ref'),node.get('pin'))]=n.get('name')

def normalize(name):
    if name=='VCC':return 'BOARD_5V'
    if name.startswith('/'):return name[1:]+'_N'
    return name.replace('USBD+','MOUSE_CLK').replace('USBD-','MOUSE_DATA')
def expect(ref,pin,name):
    assert nets[(ref,str(pin))]==name,(ref,pin,nets.get((ref,str(pin))),name)
def unused(ref,pin):
    assert nets[(ref,str(pin))].startswith('unconnected-'),(ref,pin,nets[(ref,str(pin))])

for pin,n in interface['cpc']['pins'].items():expect('J1',pin,'CPC_5V' if pin=='27' else normalize(n))
for block,ref in [('mouse_pic','U9'),('mouse_buffer','U10')]:
    for pin,n in interface[block]['pins'].items():expect(ref,pin,normalize(n))
for pin,n in interface['w5100s']['pins'].items():
    if pin in ('23','24'):unused('U8',pin)
    else:expect('U8',pin,'W5CS_N' if pin=='29' else normalize(n))
for pin,n in interface['ch376']['pins'].items():
    if n=='NC':unused('J2',pin)
    else:expect('J2',pin,'USB_5V' if pin=='5' else normalize(n))
for p in interface['pico2']['gpio']:
    n=p['signal'];expect('U1',p['module_pin'],n if n in ('ROM_LATCH','RESET_PULLDOWN') else 'P_'+normalize(n))
for pin in interface['pico2']['ground_pins']:expect('U1',pin,'GND')
expect('U1',36,'PICO_3V3');expect('U1',39,'PICO_VSYS');unused('U1',40)
pins,_=parse(ROOT/'firmware/gal/picolino.pld')
for pin,(n,inverted) in pins.items():
    expect('U2',pin,('IORQ' if n=='IOREQ' else n)+('_N' if inverted else ''))
expect('U2',12,'GND');expect('U2',24,'BOARD_5V')
for pin,n in interface['rp5c01']['proposed_connections'].items():expect('U11',pin,normalize(n))
for pin,n in {1:'RTC_BACKUP_VCC',2:'BOARD_5V',3:'GND',4:'GND',7:'RTC_POWER_GOOD',8:'VBAT'}.items():expect('U13',pin,n)
unused('U13',5);unused('U13',6)
expect('BT1',1,'VBAT');expect('BT1',2,'GND')
for pin,n in {1:'GND',2:'RTC_A0',3:'D0',4:'D1',5:'RTC_A1',6:'RTC_A2',7:'D2',8:'D3',9:'RTC_A3',10:'GND',11:'RTCAS',13:'GND',14:'GND',17:'GND',18:'GND',20:'BOARD_5V'}.items():expect('U12',pin,n)
for pin in [12,15,16,19]:unused('U12',pin)
for ref,connections in {
 'Q1':{1:'CPC_5V',2:'GND',3:'INPUT_OE_N'},
 'JP1':{1:'CPC_5V',2:'BOARD_5V',3:'EXT_5V'},
 'JP2':{1:'INPUT_OE_N',2:'DATA_OE_N',3:'BOARD_5V',4:'ROMDIS'},
 'D1':{1:'PICO_VSYS',2:'BOARD_5V'},'D6':{1:'RESET_PULLDOWN',2:'P_BUSRESET_N'},
 'J4':{1:'BOARD_5V',2:'MOUSE_DATA',3:'MOUSE_CLK',4:'GND','SH':'GND'},
 'Y1':{1:'RTC_OSCIN',2:'RTC_XOUT'},'R18':{1:'RTC_XOUT',2:'RTC_OSCOUT'},
 'CV1':{1:'RTC_OSCIN',2:'GND'},'C13':{1:'RTC_XOUT',2:'GND'},'C14':{1:'RTC_OSCOUT',2:'GND'},
}.items():
    for pin,n in connections.items():expect(ref,pin,n)
for ref,group in [('U4',[f'A{i}' for i in range(8)]),('U5',[f'A{i}' for i in range(8,14)]+['A15']),('U6',[f'D{i}' for i in range(8)]),('U7',['ROMEN_N','IORQ_N','WR_N','BUSRESET_N'])]:
    for c,n in enumerate(group,1):expect(ref,c+1,n);expect(ref,19-c,'P_'+n)
    expect(ref,10,'GND');expect(ref,20,'PICO_3V3');expect(ref,19,'DATA_OE_N' if ref=='U6' else 'INPUT_OE_N')
fp=loads((CAD/'libraries/Picolino.pretty/W5100S_Cyboard.kicad_mod').read_text())
pad_positions={p[1]:tuple(map(float,child(p,'at')[1:3])) for p in children(fp,'pad')}
for p in ET.parse(ROOT/'hardware/w5100-reference.xml').getroot().findall('pad'):
    assert pad_positions[p.get('name')]==(float(p.get('x')),-float(p.get('y')))
fp=loads((CAD/'libraries/Picolino.pretty/Pico2_Socketed.kicad_mod').read_text())
pad_positions={p[1]:tuple(map(float,child(p,'at')[1:3])) for p in children(fp,'pad')}
for pin,xy in {'1':(0,0),'20':(0,48.26),'21':(17.78,48.26),'40':(17.78,0)}.items():assert pad_positions[pin]==xy
print('PASS: CPC/Pico/PIC/W5100S/CH376 pin maps, GAL firmware pins, RTC/supervisor/oscillator topology, reset polarity and module pad geometry')
